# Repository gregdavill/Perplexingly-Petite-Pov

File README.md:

# Perplexingly-Petite-Pov
A collection of small LED based PCBs.
---

*Current Status: Design Proof of concepts.*

See README of each project to see further details.

---
## idea_001
Based on a Lattice iCE40LP FPGA.

## idea_002
Based on a Microchip SAMD11

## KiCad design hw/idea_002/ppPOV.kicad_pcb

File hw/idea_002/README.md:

# Perplexingly-Petite-Pov
A VERY small ARM Microcontroller based 20 pixel POV module.
---

*Current Status: Design Proof of concept.*

---
## Board render

## Pricipal of Operation

The PCB is intended to be mounted at the edge of a computer fan, it should have all the hardware required to syncronise to the RPM, and keep time, display a rolling text Marquee.

Ideally the two rows of LEDs will be syncronised to provide a high pixel density. Two colours may be possible, but colud be tricky due to the charliplexing.

## Hardware
 - Microchip ATSAMD11 32bit ARM M0+ 😍
 - High speed Hall Effect Sensor 😁
 - 20x 0201 charliplexed LEDs 🤪
 - All within a 6.35mm x 6.35mm 4 layer PCB! 😨🤯

## Schematic

## Firmware

The Firmware has not been written yet, once the hardware is prototyped we can throw this over the cubicle wall to the firmware team. This will likely be running very simple barematel cade, all within a super loop to keep update rates high on the charliplexed display.

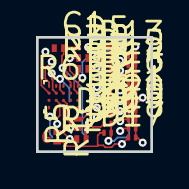
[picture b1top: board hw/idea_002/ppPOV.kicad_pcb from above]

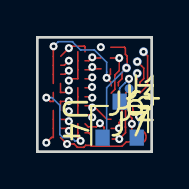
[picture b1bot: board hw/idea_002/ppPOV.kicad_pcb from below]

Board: 4 copper layers, 6.3 x 6.4 mm, 34 parts (6 on the bottom side), 16 nets.

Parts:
C1: 100nF; C_0201_NoSilk
D1, D2, D3, D4, D5, D6, D7, D8, D9, D10, D11, D12, D13, D14, D15, D16, D17, D18, D19, D20: LED; 0201_led
J1, J2, J3, J6, J7: TEST_1P; Measurement_Point_Round-SMD-Pad_Small
R1, R2, R3, R4, R5: 68R; R_0201_NoSilk
R6: R; R_0201_NoSilk
U1: ATSAMD11D14A-UUT; WLCSP-20_1.93x2.43mm_Pitch0.4mm
U4: DRV5023; SOT-23

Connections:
+3V3: C1.1, J6.1, R6.1, U1.B1, U4.1
/LED_0: D17.2, D18.2, D19.2, D20.2, R5.1, U1.C3
/LED_1: D13.2, D14.2, D15.2, D16.2, R4.1, U1.A1
/LED_2: D9.2, D10.2, D11.2, D12.2, R3.1, U1.A2
/LED_3: D5.2, D6.2, D7.2, D8.2, R2.1, U1.C4
/LED_4: D1.2, D2.2, D3.2, D4.2, R1.1, U1.D3
/RESET: J1.1, U1.E2
/SWCLK: J2.1, U1.D2
/SWDIO: J3.1, U1.E1
GND: C1.2, J7.1, U1.C2, U4.3
HALL_EFFECT: U1.D4, U4.2
unnamed: D1.1, D10.1, D14.1, D18.1, R2.2
unnamed: D3.1, D7.1, D11.1, D20.1, R4.2
unnamed: D4.1, D8.1, D12.1, D16.1, R5.2
unnamed: D5.1, D9.1, D13.1, D17.1, R1.2
unnamed: D2.1, D6.1, D15.1, D19.1, R3.2

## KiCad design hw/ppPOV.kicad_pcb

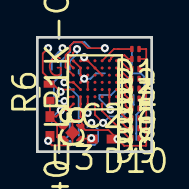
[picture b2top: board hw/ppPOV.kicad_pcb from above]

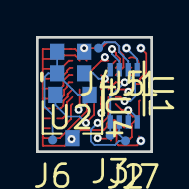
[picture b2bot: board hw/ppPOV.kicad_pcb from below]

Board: 4 copper layers, 6.3 x 6.4 mm, 25 parts (10 on the bottom side), 20 nets.

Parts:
C2: 1uF; C_0402_NoSilk
C8: 100nF; C_0402_NoSilk
D1, D2, D3, D4, D5, D6, D7, D8, D9, D10: LED_ALT; 0201_led
J1, J2, J3, J4, J5, J6, J7: TEST_1P; Measurement_Point_Round-SMD-Pad_Small
R6: R; R_0402
U1: AT25SF041; DFN-8-1EP_3x2mm_Pitch0.5mm
U2: SiT8008B; CDFN3225-4LD-PL-1
U3: TLV733P; TI_X2SON-4_1x1mm_Pitch0.65mm
U4: DRV5023; SC-59
U6: ﻿iCE40-LP1K-CM49; VFBGA-49

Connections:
+1V2: C2.1, U3.1, U6.C3, U6.D2, U6.E1, U6.F1
+3V3: C8.1, J6.1, R6.1, U1.3, U1.7, U1.8, U2.1, U2.4, U3.3, U3.4, U4.1, U6.B5, U6.B6, U6.B7, U6.G2, U6.G7
CLK: U2.3, U6.G3
CRESET: J1.1, R6.2, U6.G5
GND: C2.2, C8.2, D1.1, D2.1, D3.1, D4.1, D5.1, D6.1, D7.1, D8.1, D9.1, D10.1, J7.1, U1.4, U2.2, U3.2, U4.3, U6.E3, U6.E4, U6.E5, U6.F2, U6.F3, U6.F4, U6.G1
HALL_EFFECT: U4.2, U6.D7
LED0: D1.2, U6.C1
LED1: D2.2, U6.B1
LED2: D3.2, U6.A1
LED3: D4.2, U6.A2
LED4: D5.2, U6.A3
LED5: D6.2, U6.A4
LED6: D7.2, U6.A5
LED7: D8.2, U6.A6
LED8: D9.2, U6.A7
LED9: D10.2, U6.C7
SCK: J2.1, U1.6, U6.F6, U6.F7
SDI: J3.1, U1.5, U6.F5, U6.G4
SDO: J4.1, U1.2, U6.G6
SS: J5.1, U1.1, U6.E6, U6.E7

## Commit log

2018-09-15 Initial Commit of KiCad project files.
2018-09-15 Updated footprints folder.
2018-09-15 Added schematic to README
2018-09-15 - Spelling corrections. - Added new pcb. ATSAMD11 Based. - Refactored folders to promote reuse.
